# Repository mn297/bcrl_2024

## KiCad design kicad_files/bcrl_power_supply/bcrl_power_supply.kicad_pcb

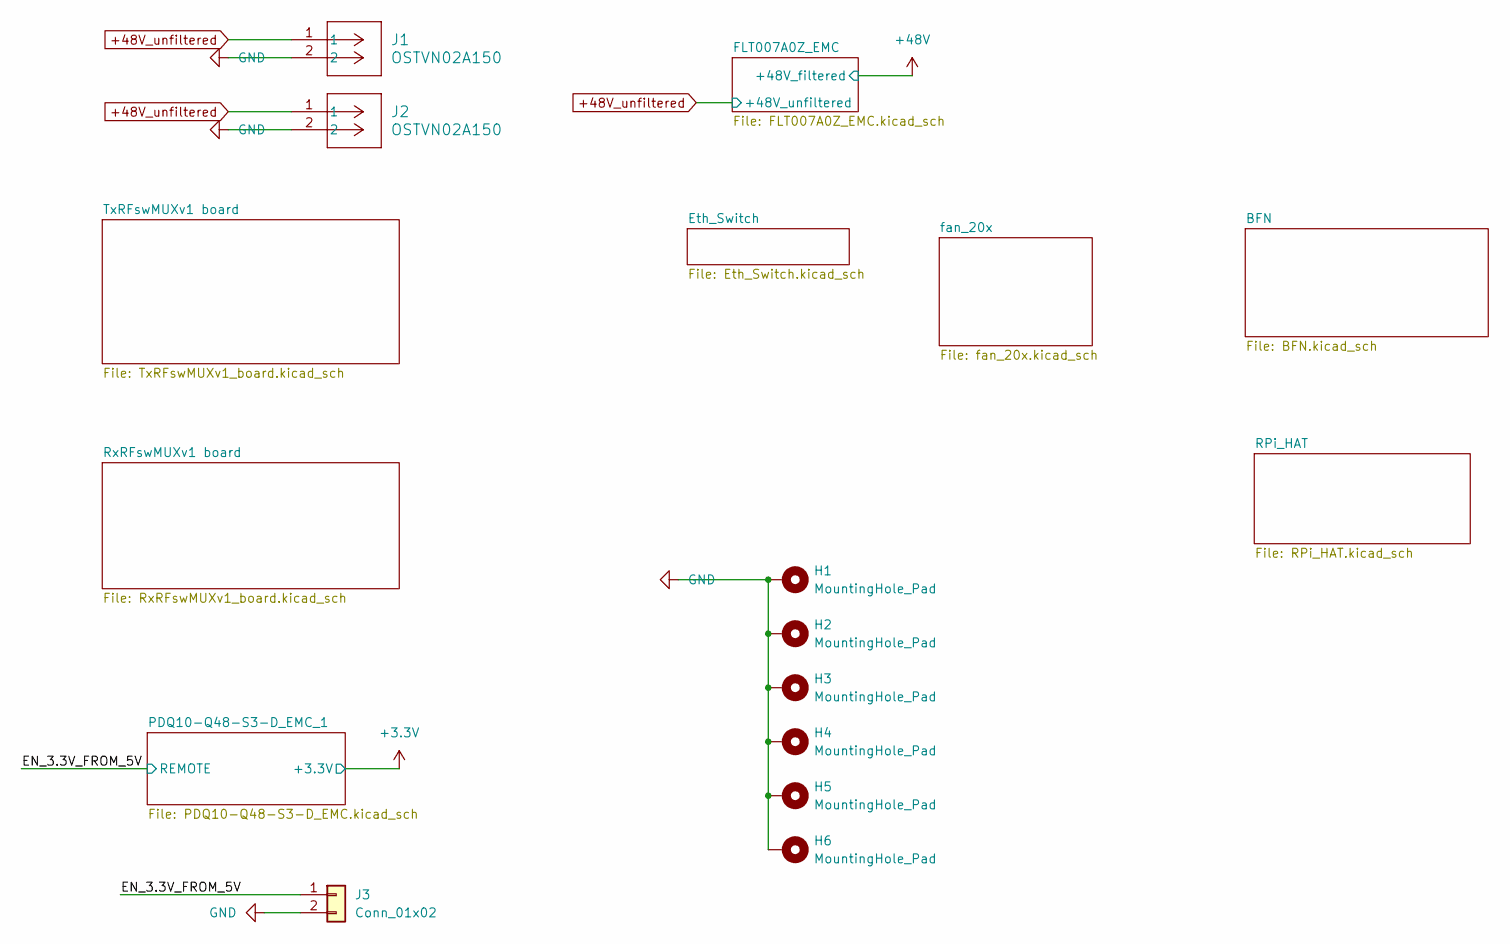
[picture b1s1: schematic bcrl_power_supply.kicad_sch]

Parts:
H1, H2, H3, H4, H5, H6: MountingHole_Pad; MountingHole_3.5mm_Pad
J1, J2: OSTVN02A150; CONN_OSTVN02A150_OST; DigiKey_Part_Number OSTVN02A150
J3: Conn_01x02; PinHeader_1x02_P2.54mm_Vertical

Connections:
+48V_unfiltered: J1.1, J2.1; also elsewhere on the board
/EN_3.3V_FROM_5V: J3.1; also elsewhere on the board
GND: H1.1, H2.1, H3.1, H4.1, H5.1, H6.1, J1.2, J2.2, J3.2; also elsewhere on the board

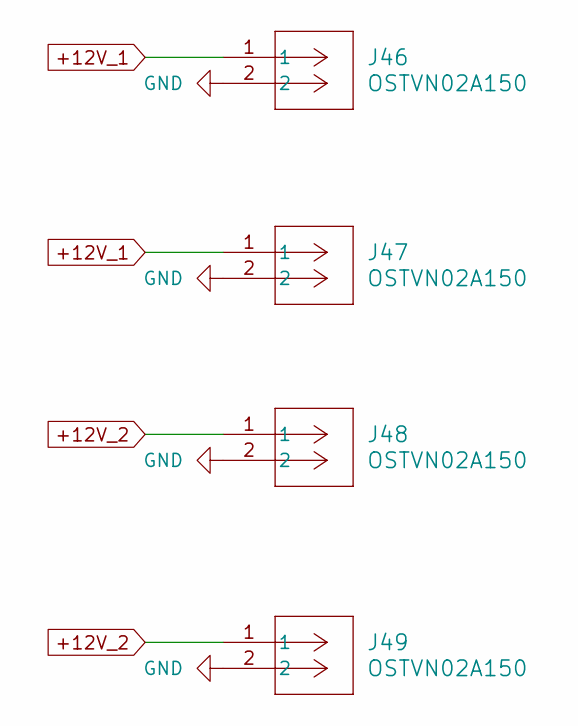
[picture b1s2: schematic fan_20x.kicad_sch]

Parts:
J46, J47, J48, J49: OSTVN02A150; CONN_OSTVN02A150_OST; DigiKey_Part_Number OSTVN02A150

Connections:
+12V_1: J46.1, J47.1; also elsewhere on the board
+12V_2: J48.1, J49.1; also elsewhere on the board
GND: J46.2, J47.2, J48.2, J49.2; also elsewhere on the board

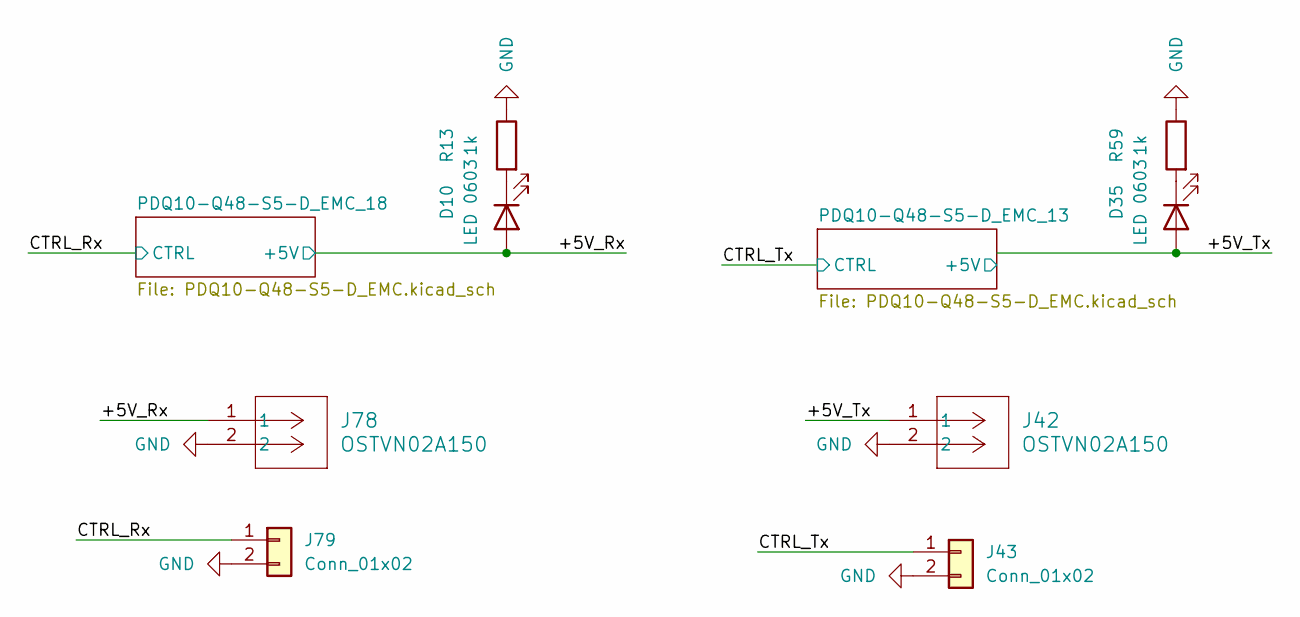
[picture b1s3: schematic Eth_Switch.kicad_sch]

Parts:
D10, D35: LED 0603; LED_0603_1608Metric; DigiKey_Part_Number 150060GS75000
J42, J78: OSTVN02A150; CONN_OSTVN02A150_OST; DigiKey_Part_Number OSTVN02A150
J43, J79: Conn_01x02; PinHeader_1x02_P2.54mm_Vertical
R13, R59: 1k; R_0603_1608Metric; DigiKey_Part_Number ESR03EZPF1001

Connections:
/Eth_Switch/+5V_Rx: D10.2 (A), J78.1; also elsewhere on the board
/Eth_Switch/+5V_Tx: D35.2 (A), J42.1
/Eth_Switch/CTRL_Rx: J79.1; also elsewhere on the board
/Eth_Switch/CTRL_Tx: J43.1; also elsewhere on the board
GND: J42.2, J43.2, J78.2, J79.2, R13.1, R59.1; also elsewhere on the board
unnamed: D10.1 (K), R13.2
unnamed: D35.1 (K), R59.2

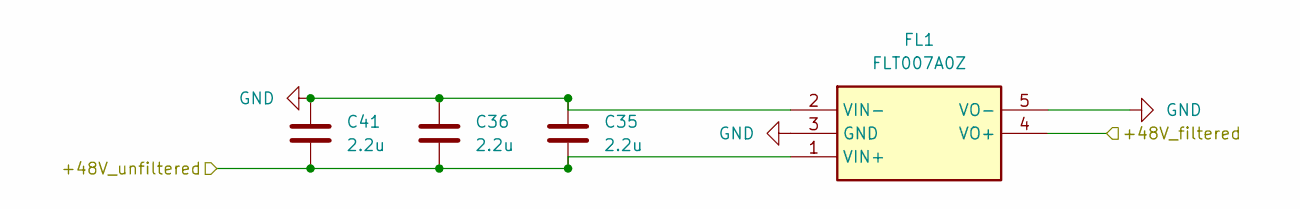
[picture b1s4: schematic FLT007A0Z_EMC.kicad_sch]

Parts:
C35, C36, C41: 2.2u; C_1206_3216Metric; rating 100v; DigiKey_Part_Number HMK316AC7225KL-TE
FL1: FLT007A0Z; Mouser Part Number 894-FLT007A0Z

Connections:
+48V: FL1.4 (VO+); also elsewhere on the board
+48V_unfiltered: C35.2, C36.2, C41.2, FL1.1 (VIN+); also elsewhere on the board
GND: C35.1, C36.1, C41.1, FL1.2 (VIN-), FL1.3 (GND), FL1.5 (VO-); also elsewhere on the board

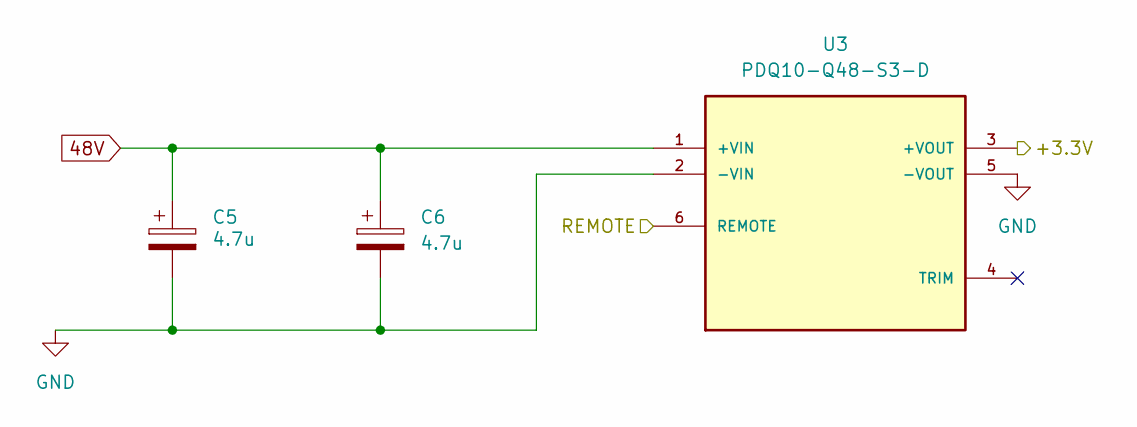
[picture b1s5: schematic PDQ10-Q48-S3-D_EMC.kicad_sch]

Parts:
C5, C6: 4.7u; C_1206_3216Metric; rating 100v; LCSC C784420
U3: PDQ10-Q48-S3-D; CONV_PDQ10-Q48-S3-D; PARTREV 1.0; DigiKey_Part_Number PDQ10-Q48-S3-D

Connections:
48V: C5.1, C6.1, U3.1 (+VIN); also elsewhere on the board
+3.3V: U3.3 (+VOUT); also elsewhere on the board
/EN_3.3V_FROM_5V: U3.6 (REMOTE); also elsewhere on the board
GND: C5.2, C6.2, U3.2 (-VIN), U3.5 (-VOUT); also elsewhere on the board

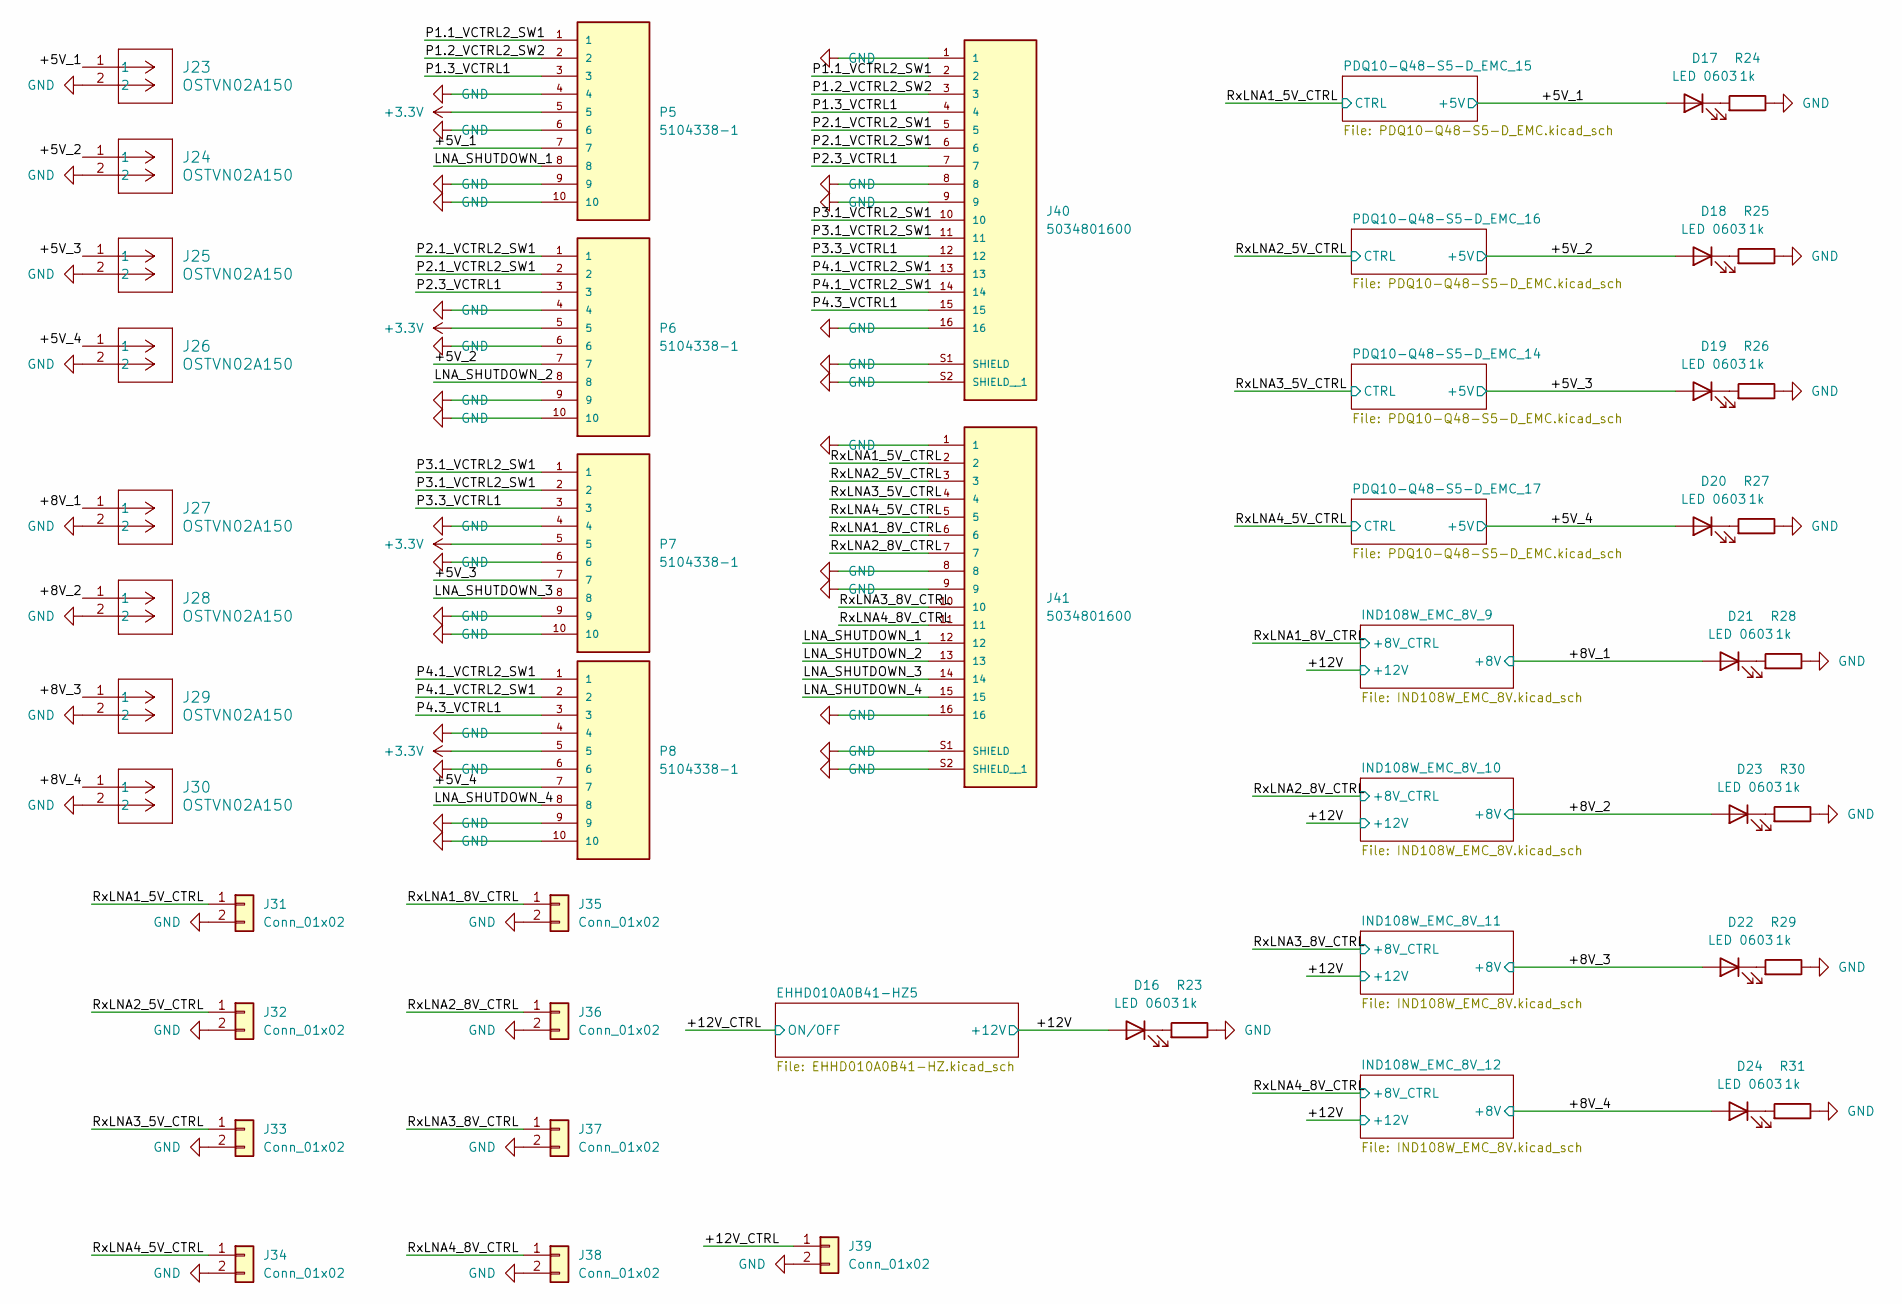
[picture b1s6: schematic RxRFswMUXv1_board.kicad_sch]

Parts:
D16, D17, D18, D19, D20, D21, D22, D23, D24: LED 0603; LED_0603_1608Metric; DigiKey_Part_Number 150060GS75000
J23, J24, J25, J26, J27, J28, J29, J30: OSTVN02A150; CONN_OSTVN02A150_OST; DigiKey_Part_Number OSTVN02A150
J31, J32, J33, J34, J35, J36, J37, J38, J39: Conn_01x02; PinHeader_1x02_P2.54mm_Vertical
J40, J41: 5034801600; MOLEX_5034801600; DigiKey_Part_Number 5034801600
P5, P6, P7, P8: 5104338-1; TE_5104338-1; PARTREV R; DigiKey_Part_Number 5104338-1
R23, R24, R25, R26, R27, R28, R29, R30, R31: 1k; R_0603_1608Metric; DigiKey_Part_Number ESR03EZPF1001

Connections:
+3.3V: P5.5, P6.5, P7.5, P8.5; also elsewhere on the board
/RxRFswMUXv1 board/+5V_1: D17.2 (A), J23.1, P5.7; also elsewhere on the board
/RxRFswMUXv1 board/+5V_2: D18.2 (A), J24.1, P6.7; also elsewhere on the board
/RxRFswMUXv1 board/+5V_3: D19.2 (A), J25.1, P7.7; also elsewhere on the board
/RxRFswMUXv1 board/+5V_4: D20.2 (A), J26.1, P8.7; also elsewhere on the board
/RxRFswMUXv1 board/+8V_1: D21.2 (A), J27.1; also elsewhere on the board
/RxRFswMUXv1 board/+8V_2: D23.2 (A), J28.1; also elsewhere on the board
/RxRFswMUXv1 board/+8V_3: D22.2 (A), J29.1; also elsewhere on the board
/RxRFswMUXv1 board/+8V_4: D24.2 (A), J30.1; also elsewhere on the board
/RxRFswMUXv1 board/+12V: D16.2 (A); also elsewhere on the board
/RxRFswMUXv1 board/+12V_CTRL: J39.1; also elsewhere on the board
/RxRFswMUXv1 board/LNA_SHUTDOWN_1: J41.12, P5.8
/RxRFswMUXv1 board/LNA_SHUTDOWN_2: J41.13, P6.8
/RxRFswMUXv1 board/LNA_SHUTDOWN_3: J41.14, P7.8
/RxRFswMUXv1 board/LNA_SHUTDOWN_4: J41.15, P8.8
/RxRFswMUXv1 board/P1.1_VCTRL2_SW1: J40.2, P5.1
/RxRFswMUXv1 board/P1.2_VCTRL2_SW2: J40.3, P5.2
/RxRFswMUXv1 board/P1.3_VCTRL1: J40.4, P5.3
/RxRFswMUXv1 board/P2.1_VCTRL2_SW1: J40.5, J40.6, P6.1, P6.2
/RxRFswMUXv1 board/P2.3_VCTRL1: J40.7, P6.3
/RxRFswMUXv1 board/P3.1_VCTRL2_SW1: J40.10, J40.11, P7.1, P7.2
/RxRFswMUXv1 board/P3.3_VCTRL1: J40.12, P7.3
/RxRFswMUXv1 board/P4.1_VCTRL2_SW1: J40.13, J40.14, P8.1, P8.2
/RxRFswMUXv1 board/P4.3_VCTRL1: J40.15, P8.3
/RxRFswMUXv1 board/RxLNA1_5V_CTRL: J31.1, J41.2; also elsewhere on the board
/RxRFswMUXv1 board/RxLNA1_8V_CTRL: J35.1, J41.6; also elsewhere on the board
/RxRFswMUXv1 board/RxLNA2_5V_CTRL: J32.1, J41.3; also elsewhere on the board
/RxRFswMUXv1 board/RxLNA2_8V_CTRL: J36.1, J41.7; also elsewhere on the board
/RxRFswMUXv1 board/RxLNA3_5V_CTRL: J33.1, J41.4; also elsewhere on the board
/RxRFswMUXv1 board/RxLNA3_8V_CTRL: J37.1, J41.10; also elsewhere on the board
/RxRFswMUXv1 board/RxLNA4_5V_CTRL: J34.1, J41.5; also elsewhere on the board
/RxRFswMUXv1 board/RxLNA4_8V_CTRL: J38.1, J41.11; also elsewhere on the board
GND: J23.2, J24.2, J25.2, J26.2, J27.2, J28.2, J29.2, J30.2, J31.2, J32.2, J33.2, J34.2, J35.2, J36.2, J37.2, J38.2, J39.2, J40.1, J40.8, J40.9, J40.16, J40.S1 (SHIELD), J40.S2 (SHIELD__1), J41.1, J41.8, J41.9, J41.16, J41.S1 (SHIELD), J41.S2 (SHIELD__1), P5.4, P5.6, P5.9, P5.10, P6.4, P6.6, P6.9, P6.10, P7.4, P7.6, P7.9, P7.10, P8.4, P8.6, P8.9, P8.10, R23.1, R24.1, R25.1, R26.1, R27.1, R28.1, R29.1, R30.1, R31.1; also elsewhere on the board
unnamed: D16.1 (K), R23.2
unnamed: D17.1 (K), R24.2
unnamed: D18.1 (K), R25.2
unnamed: D19.1 (K), R26.2
unnamed: D20.1 (K), R27.2
unnamed: D21.1 (K), R28.2
unnamed: D22.1 (K), R29.2
unnamed: D23.1 (K), R30.2
unnamed: D24.1 (K), R31.2

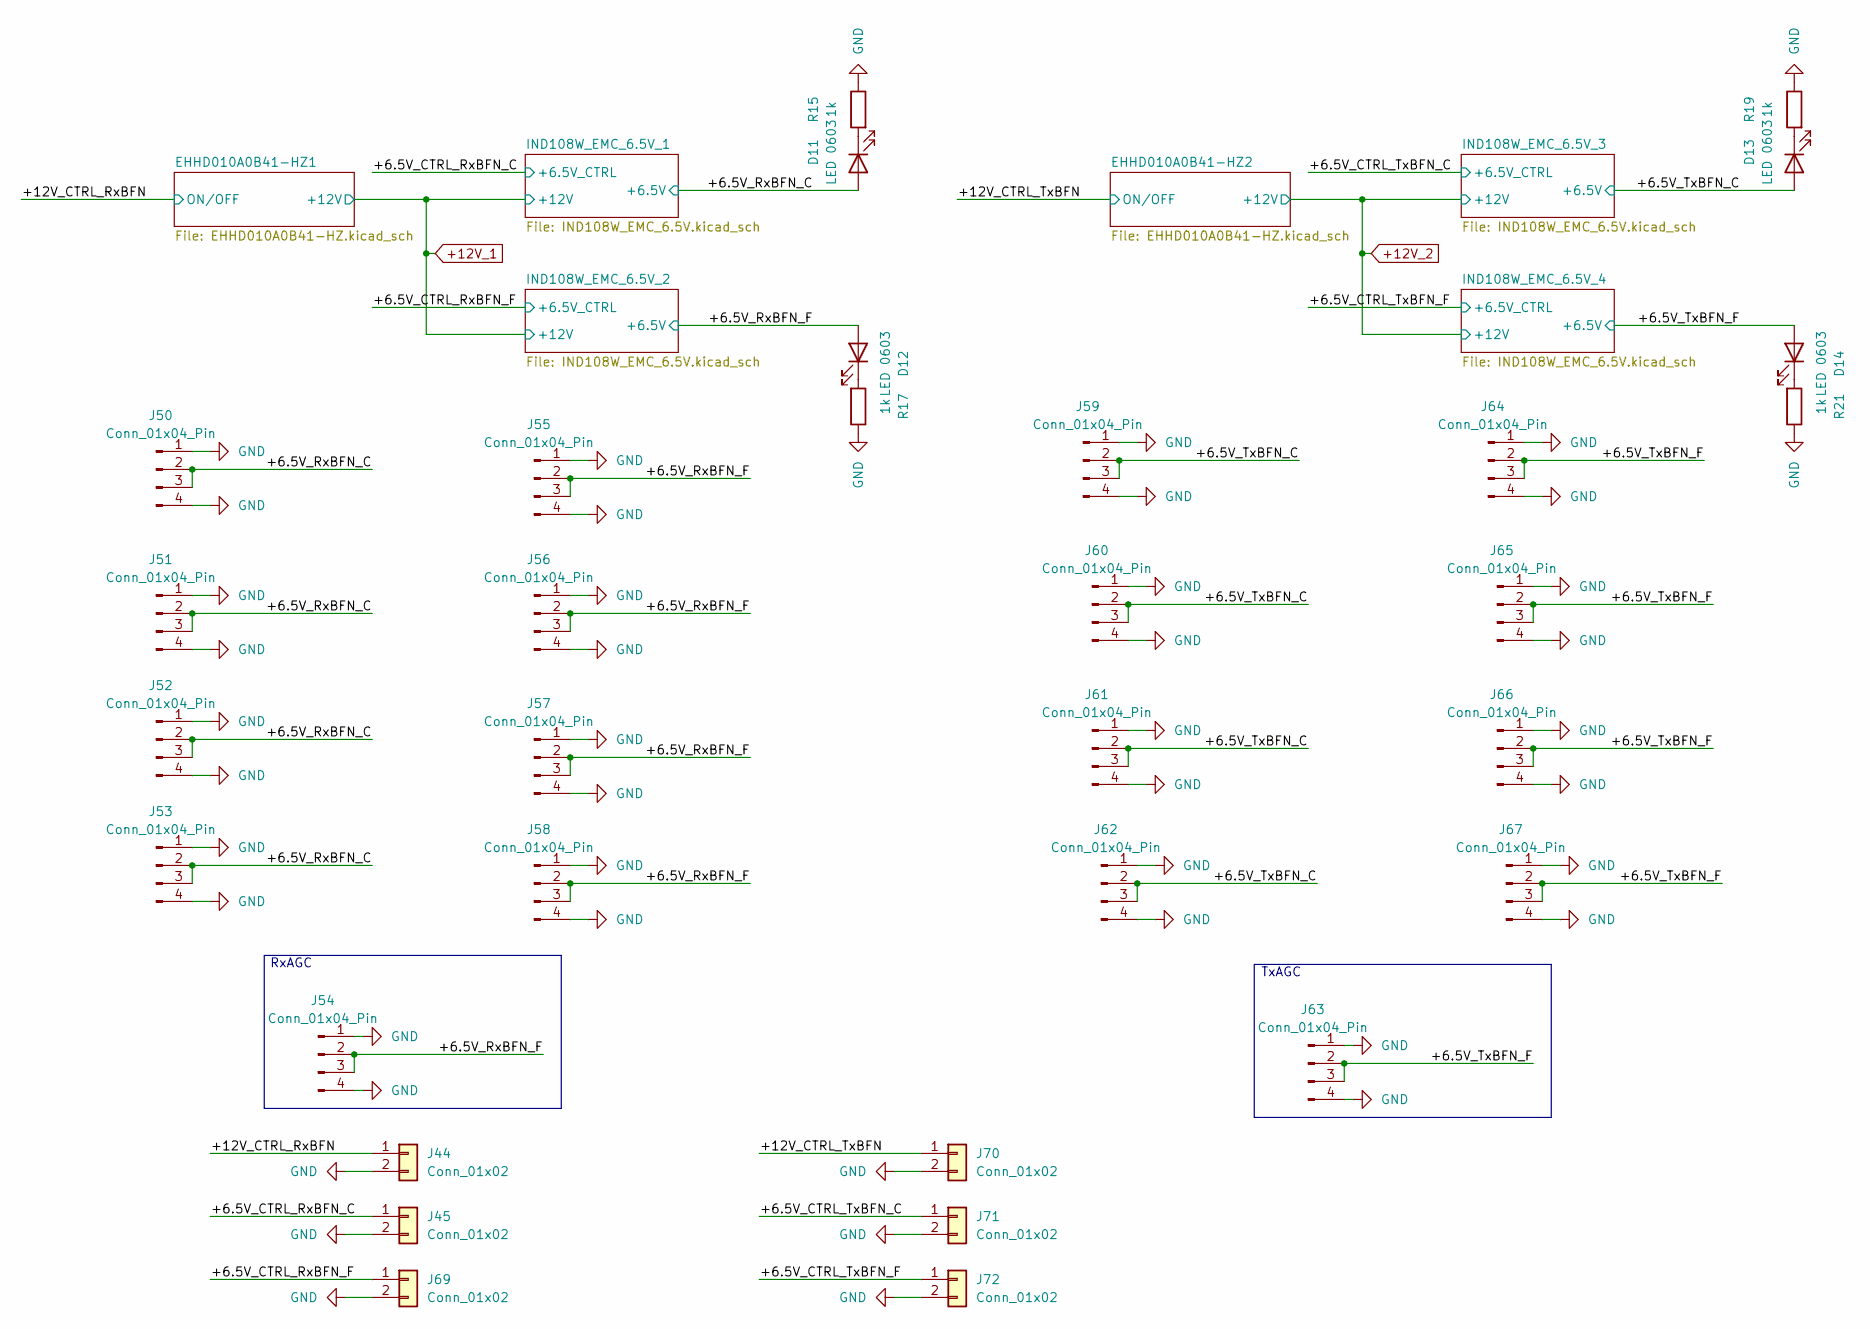
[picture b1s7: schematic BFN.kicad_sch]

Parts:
D11, D12, D13, D14: LED 0603; LED_0603_1608Metric; DigiKey_Part_Number 150060GS75000
J44, J45, J69, J70, J71, J72: Conn_01x02; PinHeader_1x02_P2.54mm_Vertical
J50, J51, J52, J53, J54, J55, J56, J57, J58, J59, J60, J61, J62, J63, J64, J65, J66, J67: Conn_01x04_Pin; PinHeader_1x04_P2.54mm_Vertical
R15, R17, R19, R21: 1k; R_0603_1608Metric; DigiKey_Part_Number ESR03EZPF1001

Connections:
/BFN/+6.5V_CTRL_RxBFN_C: J45.1; also elsewhere on the board
/BFN/+6.5V_CTRL_RxBFN_F: J69.1; also elsewhere on the board
/BFN/+6.5V_CTRL_TxBFN_C: J71.1; also elsewhere on the board
/BFN/+6.5V_CTRL_TxBFN_F: J72.1; also elsewhere on the board
/BFN/+6.5V_RxBFN_C: D11.2 (A), J50.2, J50.3, J51.2, J51.3, J52.2, J52.3, J53.2, J53.3; also elsewhere on the board
/BFN/+6.5V_RxBFN_F: D12.2 (A), J54.2, J54.3, J55.2, J55.3, J56.2, J56.3, J57.2, J57.3, J58.2, J58.3; also elsewhere on the board
/BFN/+6.5V_TxBFN_C: D13.2 (A), J59.2, J59.3, J60.2, J60.3, J61.2, J61.3, J62.2, J62.3; also elsewhere on the board
/BFN/+6.5V_TxBFN_F: D14.2 (A), J63.2, J63.3, J64.2, J64.3, J65.2, J65.3, J66.2, J66.3, J67.2, J67.3; also elsewhere on the board
/BFN/+12V_CTRL_RxBFN: J44.1; also elsewhere on the board
/BFN/+12V_CTRL_TxBFN: J70.1; also elsewhere on the board
GND: J44.2, J45.2, J50.1, J50.4, J51.1, J51.4, J52.1, J52.4, J53.1, J53.4, J54.1, J54.4, J55.1, J55.4, J56.1, J56.4, J57.1, J57.4, J58.1, J58.4, J59.1, J59.4, J60.1, J60.4, J61.1, J61.4, J62.1, J62.4, J63.1, J63.4, J64.1, J64.4, J65.1, J65.4, J66.1, J66.4, J67.1, J67.4, J69.2, J70.2, J71.2, J72.2, R15.1, R17.1, R19.1, R21.1; also elsewhere on the board
unnamed: D11.1 (K), R15.2
unnamed: D12.1 (K), R17.2
unnamed: D13.1 (K), R19.2
unnamed: D14.1 (K), R21.2

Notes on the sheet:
RxAGC
TxAGC

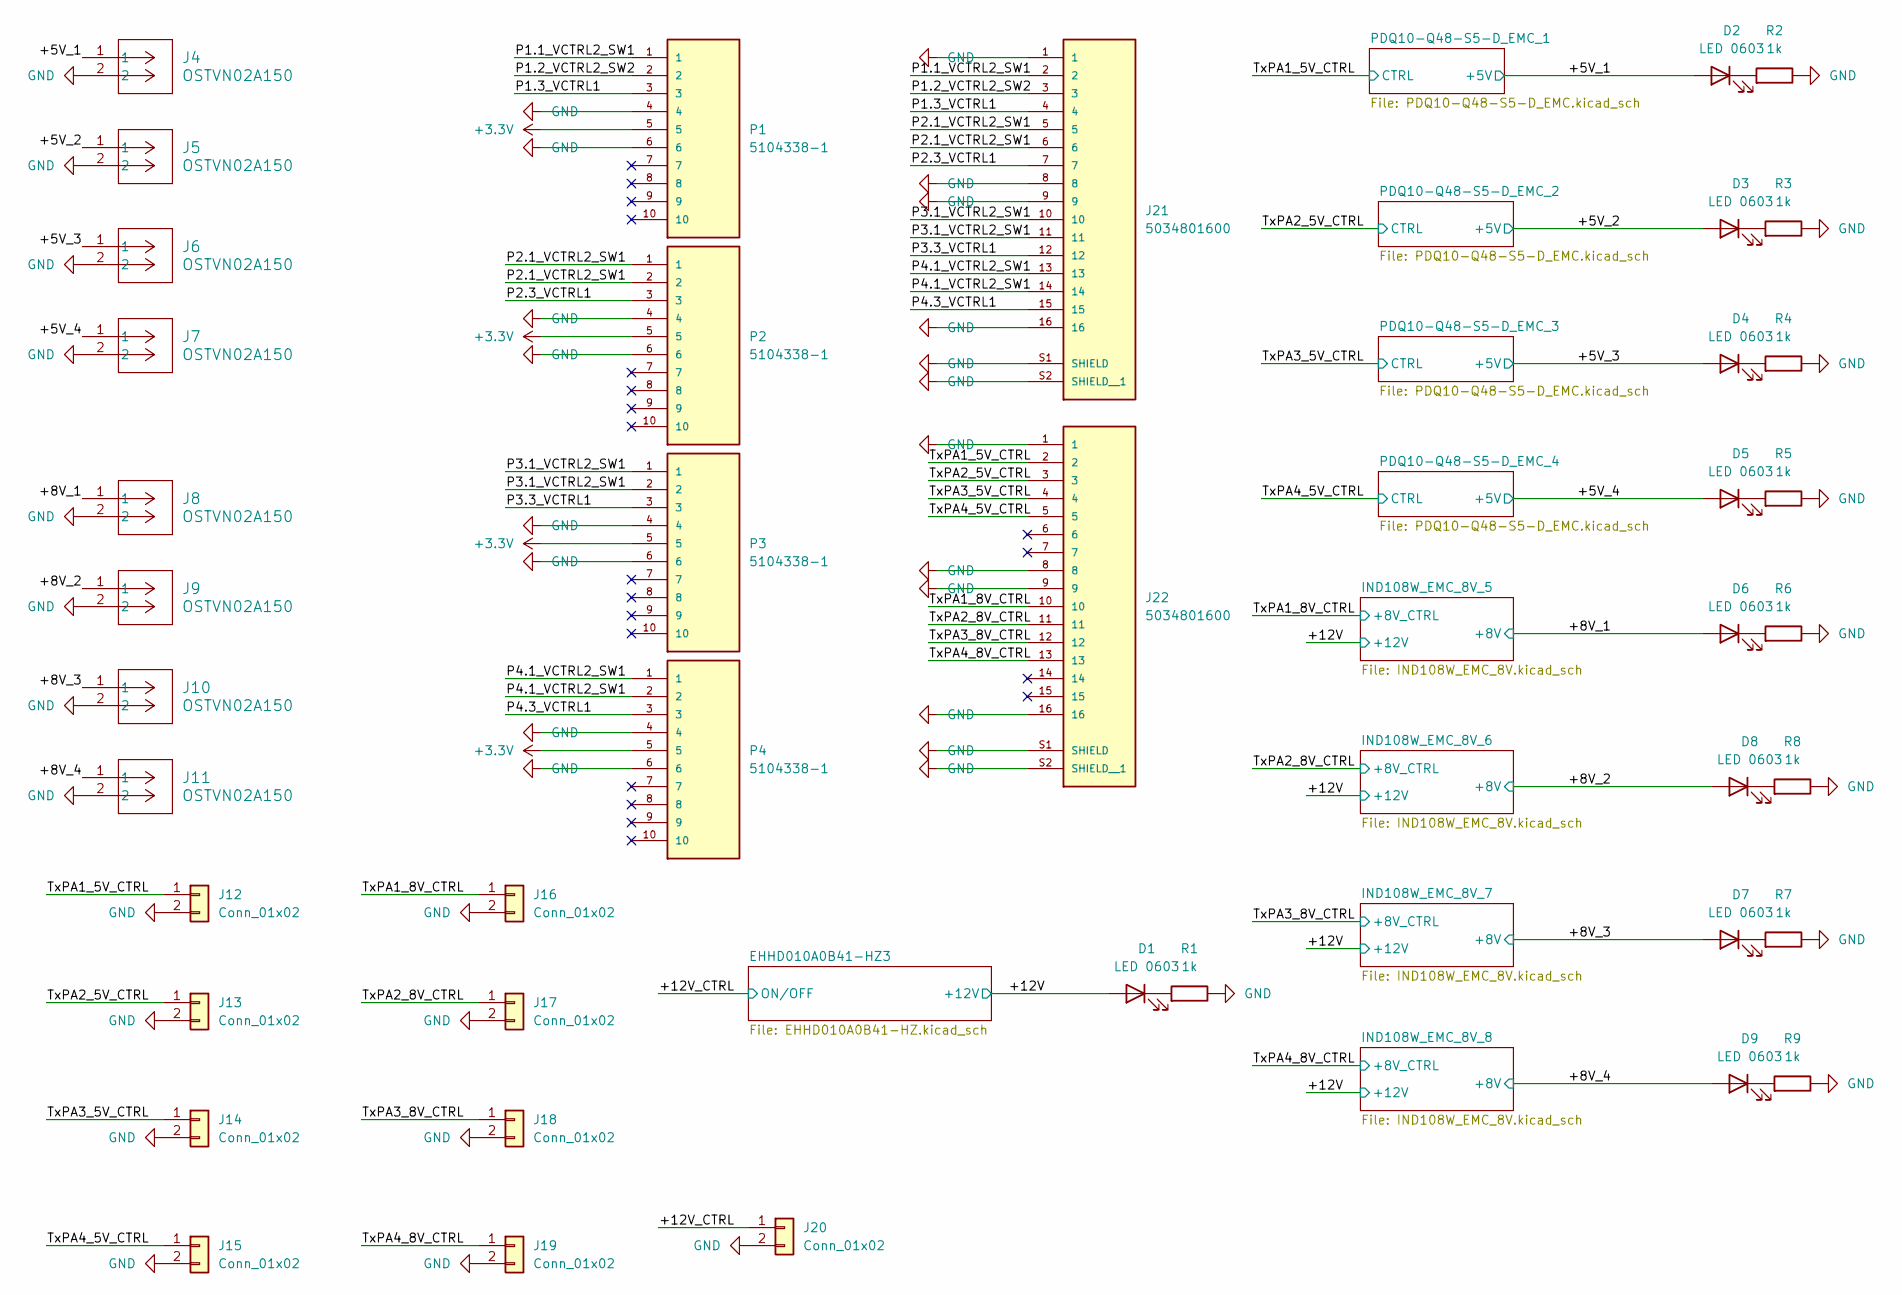
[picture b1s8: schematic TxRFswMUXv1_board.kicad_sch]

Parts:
D1, D2, D3, D4, D5, D6, D7, D8, D9: LED 0603; LED_0603_1608Metric; DigiKey_Part_Number 150060GS75000
J4, J5, J6, J7, J8, J9, J10, J11: OSTVN02A150; CONN_OSTVN02A150_OST; DigiKey_Part_Number OSTVN02A150
J12, J13, J14, J15, J16, J17, J18, J19, J20: Conn_01x02; PinHeader_1x02_P2.54mm_Vertical
J21, J22: 5034801600; MOLEX_5034801600; DigiKey_Part_Number 5034801600
P1, P2, P3, P4: 5104338-1; TE_5104338-1; PARTREV R; DigiKey_Part_Number 5104338-1
R1, R2, R3, R4, R5, R6, R7, R8, R9: 1k; R_0603_1608Metric; DigiKey_Part_Number ESR03EZPF1001

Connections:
+3.3V: P1.5, P2.5, P3.5, P4.5; also elsewhere on the board
/TxRFswMUXv1 board/+5V_1: D2.2 (A), J4.1; also elsewhere on the board
/TxRFswMUXv1 board/+5V_2: D3.2 (A), J5.1; also elsewhere on the board
/TxRFswMUXv1 board/+5V_3: D4.2 (A), J6.1; also elsewhere on the board
/TxRFswMUXv1 board/+5V_4: D5.2 (A), J7.1; also elsewhere on the board
/TxRFswMUXv1 board/+8V_1: D6.2 (A), J8.1; also elsewhere on the board
/TxRFswMUXv1 board/+8V_2: D8.2 (A), J9.1; also elsewhere on the board
/TxRFswMUXv1 board/+8V_3: D7.2 (A), J10.1; also elsewhere on the board
/TxRFswMUXv1 board/+8V_4: D9.2 (A), J11.1; also elsewhere on the board
/TxRFswMUXv1 board/+12V: D1.2 (A); also elsewhere on the board
/TxRFswMUXv1 board/+12V_CTRL: J20.1; also elsewhere on the board
/TxRFswMUXv1 board/P1.1_VCTRL2_SW1: J21.2, P1.1
/TxRFswMUXv1 board/P1.2_VCTRL2_SW2: J21.3, P1.2
/TxRFswMUXv1 board/P1.3_VCTRL1: J21.4, P1.3
/TxRFswMUXv1 board/P2.1_VCTRL2_SW1: J21.5, J21.6, P2.1, P2.2
/TxRFswMUXv1 board/P2.3_VCTRL1: J21.7, P2.3
/TxRFswMUXv1 board/P3.1_VCTRL2_SW1: J21.10, J21.11, P3.1, P3.2
/TxRFswMUXv1 board/P3.3_VCTRL1: J21.12, P3.3
/TxRFswMUXv1 board/P4.1_VCTRL2_SW1: J21.13, J21.14, P4.1, P4.2
/TxRFswMUXv1 board/P4.3_VCTRL1: J21.15, P4.3
/TxRFswMUXv1 board/TxPA1_5V_CTRL: J12.1, J22.2; also elsewhere on the board
/TxRFswMUXv1 board/TxPA1_8V_CTRL: J16.1, J22.10; also elsewhere on the board
/TxRFswMUXv1 board/TxPA2_5V_CTRL: J13.1, J22.3; also elsewhere on the board
/TxRFswMUXv1 board/TxPA2_8V_CTRL: J17.1, J22.11; also elsewhere on the board
/TxRFswMUXv1 board/TxPA3_5V_CTRL: J14.1, J22.4; also elsewhere on the board
/TxRFswMUXv1 board/TxPA3_8V_CTRL: J18.1, J22.12; also elsewhere on the board
/TxRFswMUXv1 board/TxPA4_5V_CTRL: J15.1, J22.5; also elsewhere on the board
/TxRFswMUXv1 board/TxPA4_8V_CTRL: J19.1, J22.13; also elsewhere on the board
GND: J4.2, J5.2, J6.2, J7.2, J8.2, J9.2, J10.2, J11.2, J12.2, J13.2, J14.2, J15.2, J16.2, J17.2, J18.2, J19.2, J20.2, J21.1, J21.8, J21.9, J21.16, J21.S1 (SHIELD), J21.S2 (SHIELD__1), J22.1, J22.8, J22.9, J22.16, J22.S1 (SHIELD), J22.S2 (SHIELD__1), P1.4, P1.6, P2.4, P2.6, P3.4, P3.6, P4.4, P4.6, R1.1, R2.1, R3.1, R4.1, R5.1, R6.1, R7.1, R8.1, R9.1; also elsewhere on the board
unnamed: D1.1 (K), R1.2
unnamed: D2.1 (K), R2.2
unnamed: D3.1 (K), R3.2
unnamed: D4.1 (K), R4.2
unnamed: D5.1 (K), R5.2
unnamed: D6.1 (K), R6.2
unnamed: D7.1 (K), R7.2
unnamed: D8.1 (K), R8.2
unnamed: D9.1 (K), R9.2

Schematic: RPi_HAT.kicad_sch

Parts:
D37, D38: LED 0603; LED_0603_1608Metric; DigiKey_Part_Number 150060GS75000
J68, J73, J74, J75, J80, J81, J82, J83: Conn_01x06_Pin; PinHeader_1x06_P2.54mm_Vertical
J76, J77: Conn_01x02; PinHeader_1x02_P2.54mm_Vertical
R62, R63: 1k; R_0603_1608Metric; DigiKey_Part_Number ESR03EZPF1001

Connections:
+3.3V: J68.6, J73.6, J74.6, J75.6, J80.6, J81.6, J82.6, J83.6; also elsewhere on the board
/RPi_HAT/+5V: D37.2 (A), J68.2, J73.2, J74.2, J75.2, J80.2, J81.2, J82.2, J83.2; also elsewhere on the board
/RPi_HAT/+5V_CTRL: J76.1; also elsewhere on the board
/RPi_HAT/+24V: D38.2 (A), J68.3, J73.3, J74.3, J75.3, J80.3, J81.3, J82.3, J83.3; also elsewhere on the board
/RPi_HAT/+24V_CTRL: J77.1; also elsewhere on the board
GND: J68.1, J68.4, J68.5, J73.1, J73.4, J73.5, J74.1, J74.4, J74.5, J75.1, J75.4, J75.5, J76.2, J77.2, J80.1, J80.4, J80.5, J81.1, J81.4, J81.5, J82.1, J82.4, J82.5, J83.1, J83.4, J83.5, R62.1, R63.1; also elsewhere on the board
unnamed: D37.1 (K), R62.2
unnamed: D38.1 (K), R63.2

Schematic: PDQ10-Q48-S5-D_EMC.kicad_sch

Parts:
C37, C38: 4.7u; C_1206_3216Metric; rating 100v; LCSC C784420
L4: 4.7u; L_0603_1608Metric; rating 3.1a; DigiKey_Part_Number MGAH06034R7M-10
R32: 3.4k; R_0603_1608Metric; DigiKey_Part_Number TNPW06033K40BEEA
U5: PDQ10-Q48-S5-D; CONV_PDQ10-Q48-S5-D; PARTREV 1.0; DigiKey_Part_Number PDQ10-Q48-S5-D

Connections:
48V: C37.1, L4.1; also elsewhere on the board
/Eth_Switch/CTRL_Tx: U5.6 (REMOTE); also elsewhere on the board
/Eth_Switch/PDQ10-Q48-S5-D_EMC_13/+5V: U5.3 (+VOUT)
/Eth_Switch/PDQ10-Q48-S5-D_EMC_13/VIN: C38.1, L4.2, U5.1 (+VIN)
GND: C37.2, C38.2, R32.1, U5.2 (-VIN), U5.5 (-VOUT); also elsewhere on the board
unnamed: R32.2, U5.4 (TRIM)

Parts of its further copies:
C1, C2, C3, C4, C39, C40, C50, C51, C59, C60, C61, C62, C73, C74, C75, C76, C93, C94, C129, C130: 4.7u; C_1206_3216Metric; rating 100v; LCSC C784420
L1, L2, L5, L8, L10, L11, L12, L13, L14, L15: 4.7u; L_0603_1608Metric; rating 3.1a; DigiKey_Part_Number MGAH06034R7M-10
R10, R11, R12, R37, R38, R39, R42, R43, R48, R61: 3.4k; R_0603_1608Metric; DigiKey_Part_Number TNPW06033K40BEEA
U1, U2, U6, U8, U9, U10, U11, U12, U13, U14: PDQ10-Q48-S5-D; CONV_PDQ10-Q48-S5-D; PARTREV 1.0; DigiKey_Part_Number PDQ10-Q48-S5-D

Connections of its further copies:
48V: C1.1, C3.1, C39.1, C50.1, C59.1, C61.1, C73.1, C75.1, C93.1, C129.1, L1.1, L2.1, L5.1, L8.1, L10.1, L11.1, L12.1, L13.1, L14.1, L15.1; also elsewhere on the board
/Eth_Switch/+5V_Rx: U6.3 (+VOUT); also elsewhere on the board
/Eth_Switch/CTRL_Rx: U6.6 (REMOTE); also elsewhere on the board
/Eth_Switch/PDQ10-Q48-S5-D_EMC_18/VIN: C40.1, L5.2, U6.1 (+VIN)
/RPi_HAT/+5V: U14.3 (+VOUT); also elsewhere on the board
/RPi_HAT/+5V_CTRL: U14.6 (REMOTE); also elsewhere on the board
/RPi_HAT/PDQ10-Q48-S5-D_EMC_9/VIN: C130.1, L15.2, U14.1 (+VIN)
/RxRFswMUXv1 board/+5V_1: U9.3 (+VOUT); also elsewhere on the board
/RxRFswMUXv1 board/+5V_2: U11.3 (+VOUT); also elsewhere on the board
/RxRFswMUXv1 board/+5V_3: U8.3 (+VOUT); also elsewhere on the board
/RxRFswMUXv1 board/+5V_4: U12.3 (+VOUT); also elsewhere on the board
/RxRFswMUXv1 board/PDQ10-Q48-S5-D_EMC_14/VIN: C51.1, L8.2, U8.1 (+VIN)
/RxRFswMUXv1 board/PDQ10-Q48-S5-D_EMC_15/VIN: C60.1, L10.2, U9.1 (+VIN)
/RxRFswMUXv1 board/PDQ10-Q48-S5-D_EMC_16/VIN: C74.1, L12.2, U11.1 (+VIN)
/RxRFswMUXv1 board/PDQ10-Q48-S5-D_EMC_17/VIN: C76.1, L13.2, U12.1 (+VIN)
/RxRFswMUXv1 board/RxLNA1_5V_CTRL: U9.6 (REMOTE); also elsewhere on the board
/RxRFswMUXv1 board/RxLNA2_5V_CTRL: U11.6 (REMOTE); also elsewhere on the board
/RxRFswMUXv1 board/RxLNA3_5V_CTRL: U8.6 (REMOTE); also elsewhere on the board
/RxRFswMUXv1 board/RxLNA4_5V_CTRL: U12.6 (REMOTE); also elsewhere on the board
/TxRFswMUXv1 board/+5V_1: U10.3 (+VOUT); also elsewhere on the board
/TxRFswMUXv1 board/+5V_2: U13.3 (+VOUT); also elsewhere on the board
/TxRFswMUXv1 board/+5V_3: U1.3 (+VOUT); also elsewhere on the board
/TxRFswMUXv1 board/+5V_4: U2.3 (+VOUT); also elsewhere on the board
/TxRFswMUXv1 board/PDQ10-Q48-S5-D_EMC_1/VIN: C62.1, L11.2, U10.1 (+VIN)
/TxRFswMUXv1 board/PDQ10-Q48-S5-D_EMC_2/VIN: C94.1, L14.2, U13.1 (+VIN)
/TxRFswMUXv1 board/PDQ10-Q48-S5-D_EMC_3/VIN: C2.1, L1.2, U1.1 (+VIN)
/TxRFswMUXv1 board/PDQ10-Q48-S5-D_EMC_4/VIN: C4.1, L2.2, U2.1 (+VIN)
/TxRFswMUXv1 board/TxPA1_5V_CTRL: U10.6 (REMOTE); also elsewhere on the board
/TxRFswMUXv1 board/TxPA2_5V_CTRL: U13.6 (REMOTE); also elsewhere on the board
/TxRFswMUXv1 board/TxPA3_5V_CTRL: U1.6 (REMOTE); also elsewhere on the board
/TxRFswMUXv1 board/TxPA4_5V_CTRL: U2.6 (REMOTE); also elsewhere on the board
GND: C1.2, C2.2, C3.2, C4.2, C39.2, C40.2, C50.2, C51.2, C59.2, C60.2, C61.2, C62.2, C73.2, C74.2, C75.2, C76.2, C93.2, C94.2, C129.2, C130.2, R10.1, R11.1, R12.1, R37.1, R38.1, R39.1, R42.1, R43.1, R48.1, R61.1, U1.2 (-VIN), U1.5 (-VOUT), U2.2 (-VIN), U2.5 (-VOUT), U6.2 (-VIN), U6.5 (-VOUT), U8.2 (-VIN), U8.5 (-VOUT), U9.2 (-VIN), U9.5 (-VOUT), U10.2 (-VIN), U10.5 (-VOUT), U11.2 (-VIN), U11.5 (-VOUT), U12.2 (-VIN), U12.5 (-VOUT), U13.2 (-VIN), U13.5 (-VOUT), U14.2 (-VIN), U14.5 (-VOUT); also elsewhere on the board
unnamed: R10.2, U1.4 (TRIM)
unnamed: R11.2, U2.4 (TRIM)
unnamed: R12.2, U6.4 (TRIM)
unnamed: R37.2, U8.4 (TRIM)
unnamed: R38.2, U9.4 (TRIM)
unnamed: R39.2, U10.4 (TRIM)
unnamed: R42.2, U11.4 (TRIM)
unnamed: R43.2, U12.4 (TRIM)
unnamed: R48.2, U13.4 (TRIM)
unnamed: R61.2, U14.4 (TRIM)

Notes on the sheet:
Trim up 10%, 3400 ohms

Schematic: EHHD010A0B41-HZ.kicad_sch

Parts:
C31, C33: 47u; CP_Radial_D12.5mm_P5.00mm; rating 100v; DigiKey_Part_Number UCS2E470MHD1TO
C32, C34: 1u; C_0603_1608Metric; rating 50v; DigiKey_Part_Number C1608X5R1H105K080DB
PS5: EHHD010A0B41-HZ; CONV_EHHD010A0B41-HZ; DigiKey_Part_Number EHHD010A0B41-HZ

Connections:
+12V_1: C33.1, C34.1, PS5.8 (VO+); also elsewhere on the board
+48V: C31.1, C32.1, PS5.1 (VI+); also elsewhere on the board
/BFN/+12V_CTRL_RxBFN: PS5.2 (ON/OFF); also elsewhere on the board
GND: C31.2, C32.2, C33.2, C34.2, PS5.3 (VI-), PS5.4 (VO-); also elsewhere on the board

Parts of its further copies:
C42, C44, C77, C79, C101, C103: 47u; CP_Radial_D12.5mm_P5.00mm; rating 100v; DigiKey_Part_Number UCS2E470MHD1TO
C43, C45, C78, C80, C102, C104: 1u; C_0603_1608Metric; rating 50v; DigiKey_Part_Number C1608X5R1H105K080DB
PS6, PS10, PS14: EHHD010A0B41-HZ; CONV_EHHD010A0B41-HZ; DigiKey_Part_Number EHHD010A0B41-HZ

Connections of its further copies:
+12V_2: C44.1, C45.1, PS6.8 (VO+); also elsewhere on the board
+48V: C42.1, C43.1, C77.1, C78.1, C101.1, C102.1, PS6.1 (VI+), PS10.1 (VI+), PS14.1 (VI+); also elsewhere on the board
/BFN/+12V_CTRL_TxBFN: PS6.2 (ON/OFF); also elsewhere on the board
/RxRFswMUXv1 board/+12V: C79.1, C80.1, PS10.8 (VO+); also elsewhere on the board
/RxRFswMUXv1 board/+12V_CTRL: PS10.2 (ON/OFF); also elsewhere on the board
/TxRFswMUXv1 board/+12V: C103.1, C104.1, PS14.8 (VO+); also elsewhere on the board
/TxRFswMUXv1 board/+12V_CTRL: PS14.2 (ON/OFF); also elsewhere on the board
GND: C42.2, C43.2, C44.2, C45.2, C77.2, C78.2, C79.2, C80.2, C101.2, C102.2, C103.2, C104.2, PS6.3 (VI-), PS6.4 (VO-), PS10.3 (VI-), PS10.4 (VO-), PS14.3 (VI-), PS14.4 (VO-); also elsewhere on the board

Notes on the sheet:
Positive logic is to leave ON/OFF open https://www.mouser.ca/datasheet/2/167/ehhd010_ds-3395666.pdf

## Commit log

2024-01-17 first
2024-01-17 hole size
2024-01-18 ADRV9026 sketch added
2024-01-22 solidworks
2024-01-22 added antenna assembly
2024-01-23 finalized
2024-01-24 aligned
2024-01-26 added fans to panel2
2024-01-26 fixed alignment
2024-01-27 final version with full holes
2024-01-29 added BFN controller holes
2024-02-08 added
2024-02-19 added components
2024-02-19 fixed path
2024-02-21 added 8V dcdc
2024-02-21 TxMUX done
2024-02-22 .gitignore
2024-02-22 added decoupling
2024-02-26 added EMC
2024-03-01 added more circuits
2024-03-11 cleanup PCB
2024-03-11 almost done schematic
2024-03-15 schematic done
2024-03-18 started LCSC, fixing DCDC
2024-03-18 big reorg
2024-03-20 ind108w
2024-03-20 big changes
2024-03-20 changed to a4
2024-03-21 board review
2024-03-25 digikey BOM
2024-04-08 psu v2
2024-04-09 added 3d models
